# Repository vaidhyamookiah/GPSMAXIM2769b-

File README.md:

# GPSMAXIM2769b
Designed Maxim 2769b GNSS frontend PCB for open source FPGA board (Papilio one) using Eagle PCB.

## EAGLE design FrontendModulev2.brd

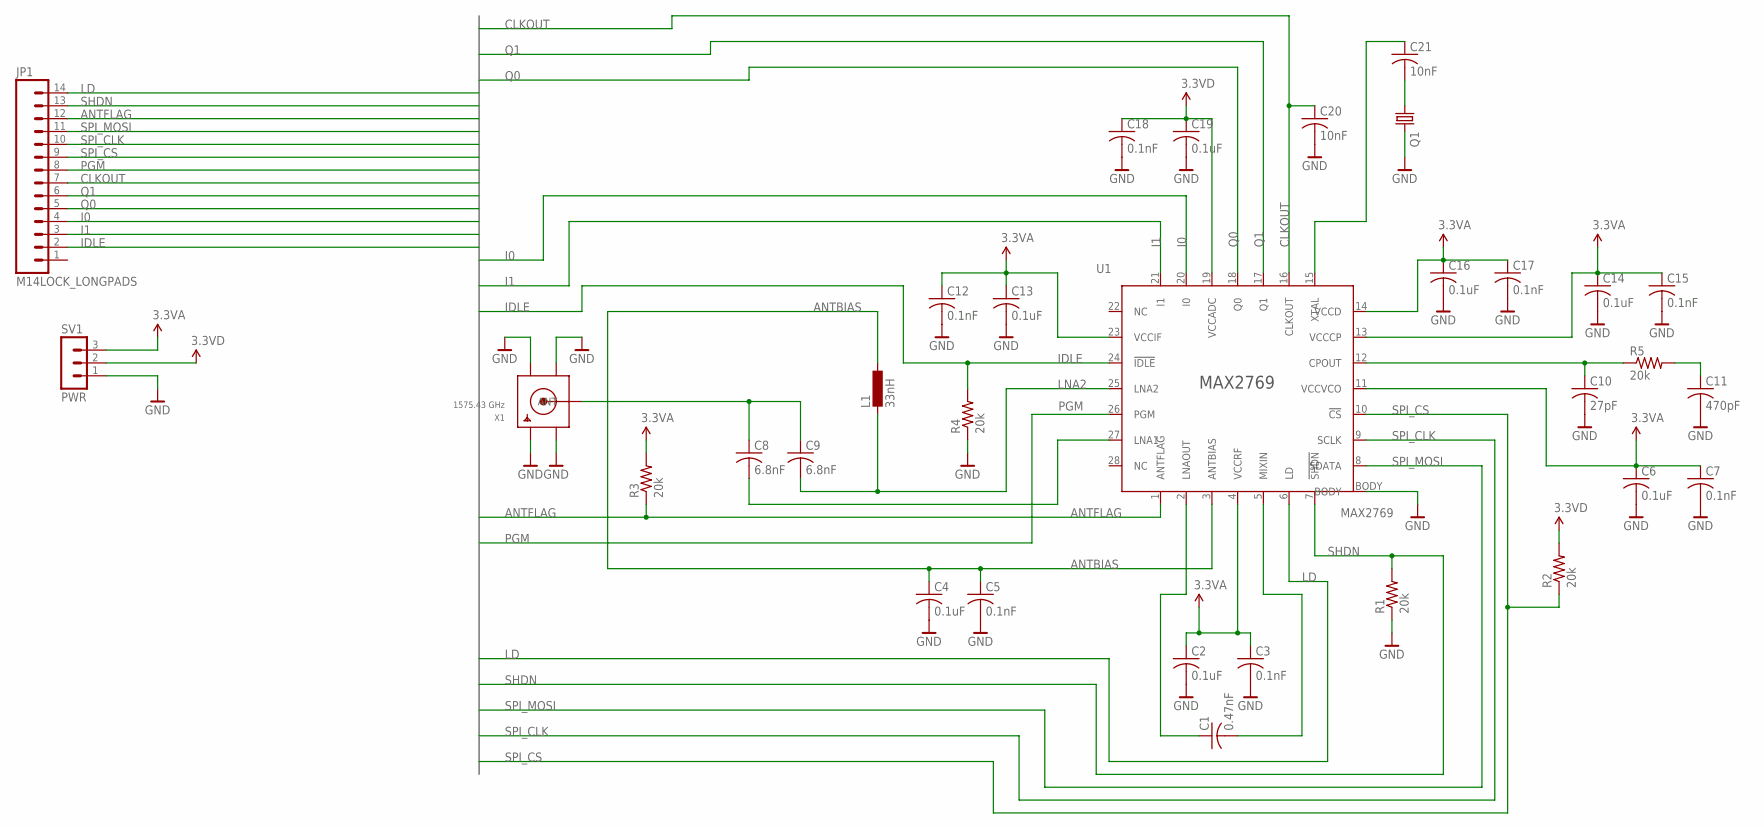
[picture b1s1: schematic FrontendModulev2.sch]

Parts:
C1: 0.47nF; C0805K
C2, C4, C6, C13, C14, C16, C19: 0.1uF; C0805K
C3, C5, C7, C12, C15, C17, C18: 0.1nF; C0805K
C8, C9: 6.8nF; C0805K
C10: 27pF; C0805K
C11: 470pF; C0805K
C20, C21: 10nF; C0805K
JP1: M14LOCK_LONGPADS; 1X14_LOCK_LONGPADS
L1: 33nH; L2012C
Q1: CRYSTALCTS406; CTS406
R1, R2, R3, R4, R5: 20k; R0805
SV1: PWR; MA03-1
U1: MAX2769; 90-0023
X1: 1575.43 GHz; SMA90_DIP

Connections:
3.3VA: C2.1, C3.1, C6.1, C7.1, C12.1, C13.1, C14.1, C15.1, C16.1, C17.1, R3.2, SV1.3, U1.4 (VCCRF), U1.11 (VCCVCO), U1.13 (VCCCP), U1.14 (VCCD), U1.23 (VCCIF)
3.3VD: C18.1, C19.1, R2.2, SV1.2, U1.19 (VCCADC)
ANTBIAS: C4.1, C5.1, L1.1, U1.3 (ANTBIAS)
ANTFLAG: JP1.12, R3.1, U1.1 (ANTFLAG)
BAR_GND: C2.2, C3.2, C4.2, C5.2, C6.2, C7.2, C10.2, C11.2, C12.2, C13.2, C14.2, C15.2, C16.2, C17.2, C18.2, C19.2, C20.2, Q1.3 (2), R1.1, R4.1, SV1.1, U1.BODY, X1.GND1, X1.GND2, X1.GND3, X1.GND4
CLKOUT: C20.1, JP1.7, U1.16 (CLKOUT)
I0: JP1.4, U1.20 (I0)
I1: JP1.3, U1.21 (I1)
IDLE: JP1.2, R4.2, U1.24 (!IDLE)
LD: JP1.14, U1.6 (LD)
LNA1: C8.2, U1.27 (LNA1)
LNA2: C9.2, L1.2, U1.25 (LNA2)
unnamed: C8.1, C9.1, X1.ANTENNA (ANT)
unnamed: C1.2, U1.5 (MIXIN)
unnamed: C21.2, Q1.1
unnamed: C10.1, R5.1, U1.12 (CPOUT)
unnamed: C11.1, R5.2
unnamed: C1.1, U1.2 (LNAOUT)
unnamed: C21.1, U1.15 (XTAL)
PGM: JP1.8, U1.26 (PGM)
Q0: JP1.5, U1.18 (Q0)
Q1: JP1.6, U1.17 (Q1)
SHDN: JP1.13, R1.2, U1.7 (!SHDN)
SPI_CLK: JP1.10, U1.9 (SCLK)
SPI_CS: JP1.9, R2.1, U1.10 (!CS)
SPI_MOSI: JP1.11, U1.8 (SDATA)

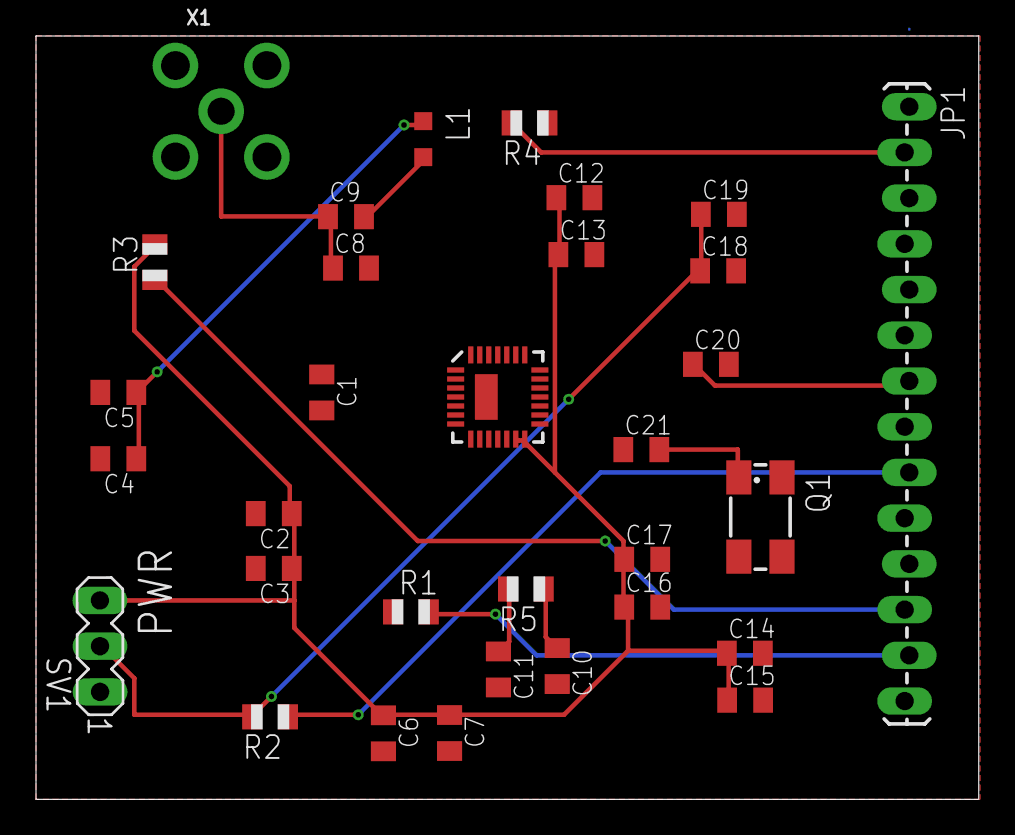
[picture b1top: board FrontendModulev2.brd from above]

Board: 2 copper layers, 52.4 x 42.4 mm, 32 parts (0 on the bottom side), 26 nets.

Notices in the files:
parts and their libraries:
SparkFun-Connectors: Licensing: CC v3.0 Share-Alike You are welcome to use this library for commercial purposes.
